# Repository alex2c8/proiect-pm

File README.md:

# ATmega DX-Ball

[DX-Ball](https://en.wikipedia.org/wiki/DX-Ball) on ATmega324A µC ([wiki](https://ocw.cs.pub.ro/courses/pm/prj2017/ddragomir/dx_ball)).

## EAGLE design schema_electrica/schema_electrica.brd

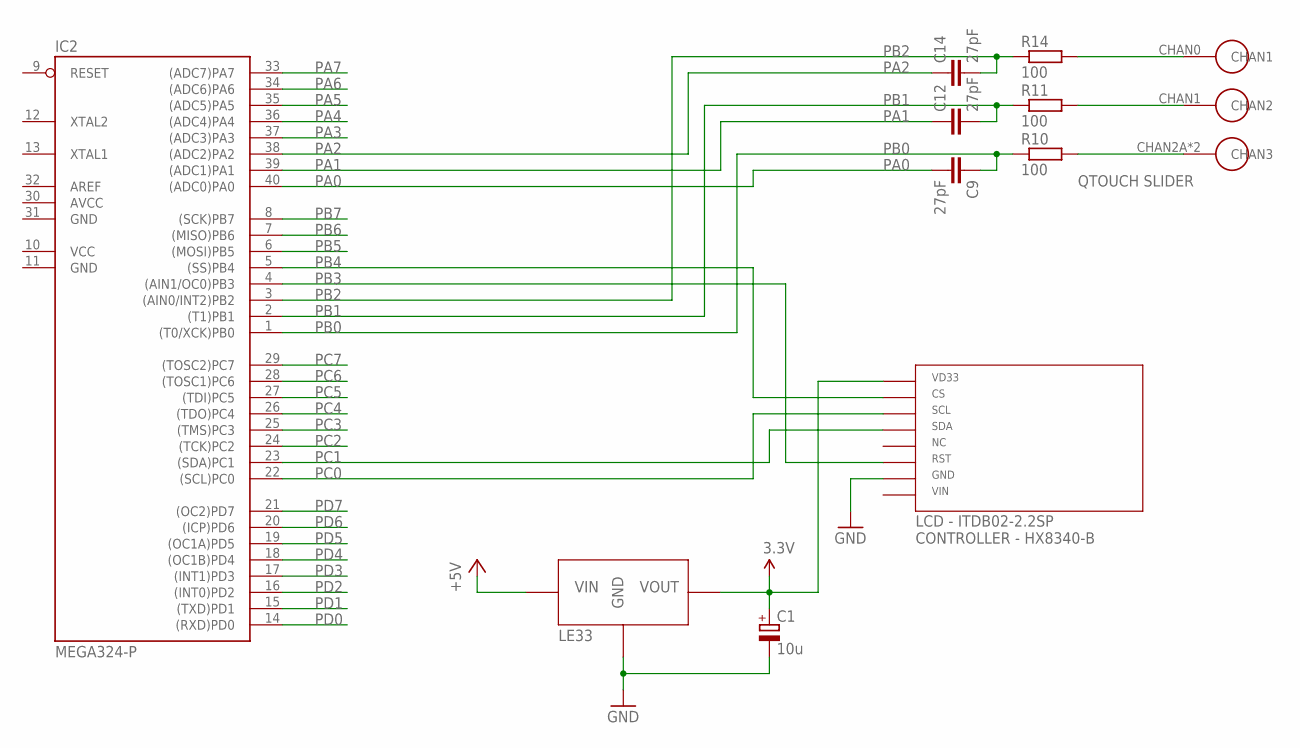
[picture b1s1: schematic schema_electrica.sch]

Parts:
C1: 10u; E2,5-5
C9, C12, C14: 27pF; C1206
IC2: MEGA324-P; DIL40
R10, R11, R14: 100; M1206
U$1: QT_SLIDER

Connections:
3.3V: C1.+
AVCC: IC2.30 (AVCC)
GND: C1.-, IC2.11 (GND), IC2.31 (GND)
unnamed: R14.2, U$1.CHAN0 (CHAN1)
unnamed: R11.2, U$1.CHAN1 (CHAN2)
unnamed: R10.2, U$1.CHAN2A (CHAN3), U$1.CHAN2B (CHAN3)
PA0: C9.2, IC2.40 ((ADC0)PA0)
PA1: C12.1, IC2.39 ((ADC1)PA1)
PA2: C14.1, IC2.38 ((ADC2)PA2)
PA3: IC2.37 ((ADC3)PA3)
PA4: IC2.36 ((ADC4)PA4)
PA5: IC2.35 ((ADC5)PA5)
PA6: IC2.34 ((ADC6)PA6)
PA7: IC2.33 ((ADC7)PA7)
PB0: C9.1, IC2.1 ((T0/XCK)PB0), R10.1
PB1: C12.2, IC2.2 ((T1)PB1), R11.1
PB2: C14.2, IC2.3 ((AIN0/INT2)PB2), R14.1
PB3: IC2.4 ((AIN1/OC0)PB3)
PB4: IC2.5 ((SS)PB4)
PB5: IC2.6 ((MOSI)PB5)
PB6: IC2.7 ((MISO)PB6)
PB7: IC2.8 ((SCK)PB7)
PC0: IC2.22 ((SCL)PC0)
PC1: IC2.23 ((SDA)PC1)
PC2: IC2.24 ((TCK)PC2)
PC3: IC2.25 ((TMS)PC3)
PC4: IC2.26 ((TDO)PC4)
PC5: IC2.27 ((TDI)PC5)
PC6: IC2.28 ((TOSC1)PC6)
PC7: IC2.29 ((TOSC2)PC7)
PD0: IC2.14 ((RXD)PD0)
PD1: IC2.15 ((TXD)PD1)
PD2: IC2.16 ((INT0)PD2)
PD3: IC2.17 ((INT1)PD3)
PD4: IC2.18 ((OC1B)PD4)
PD5: IC2.19 ((OC1A)PD5)
PD6: IC2.20 ((ICP)PD6)
PD7: IC2.21 ((OC2)PD7)
VCC: IC2.10 (VCC)

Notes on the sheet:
VD33
SCL
SDA
RST
GND
VIN
LCD - ITDB02-2.2SP CONTROLLER - HX8340-B
QTOUCH SLIDER
VOUT
LE33

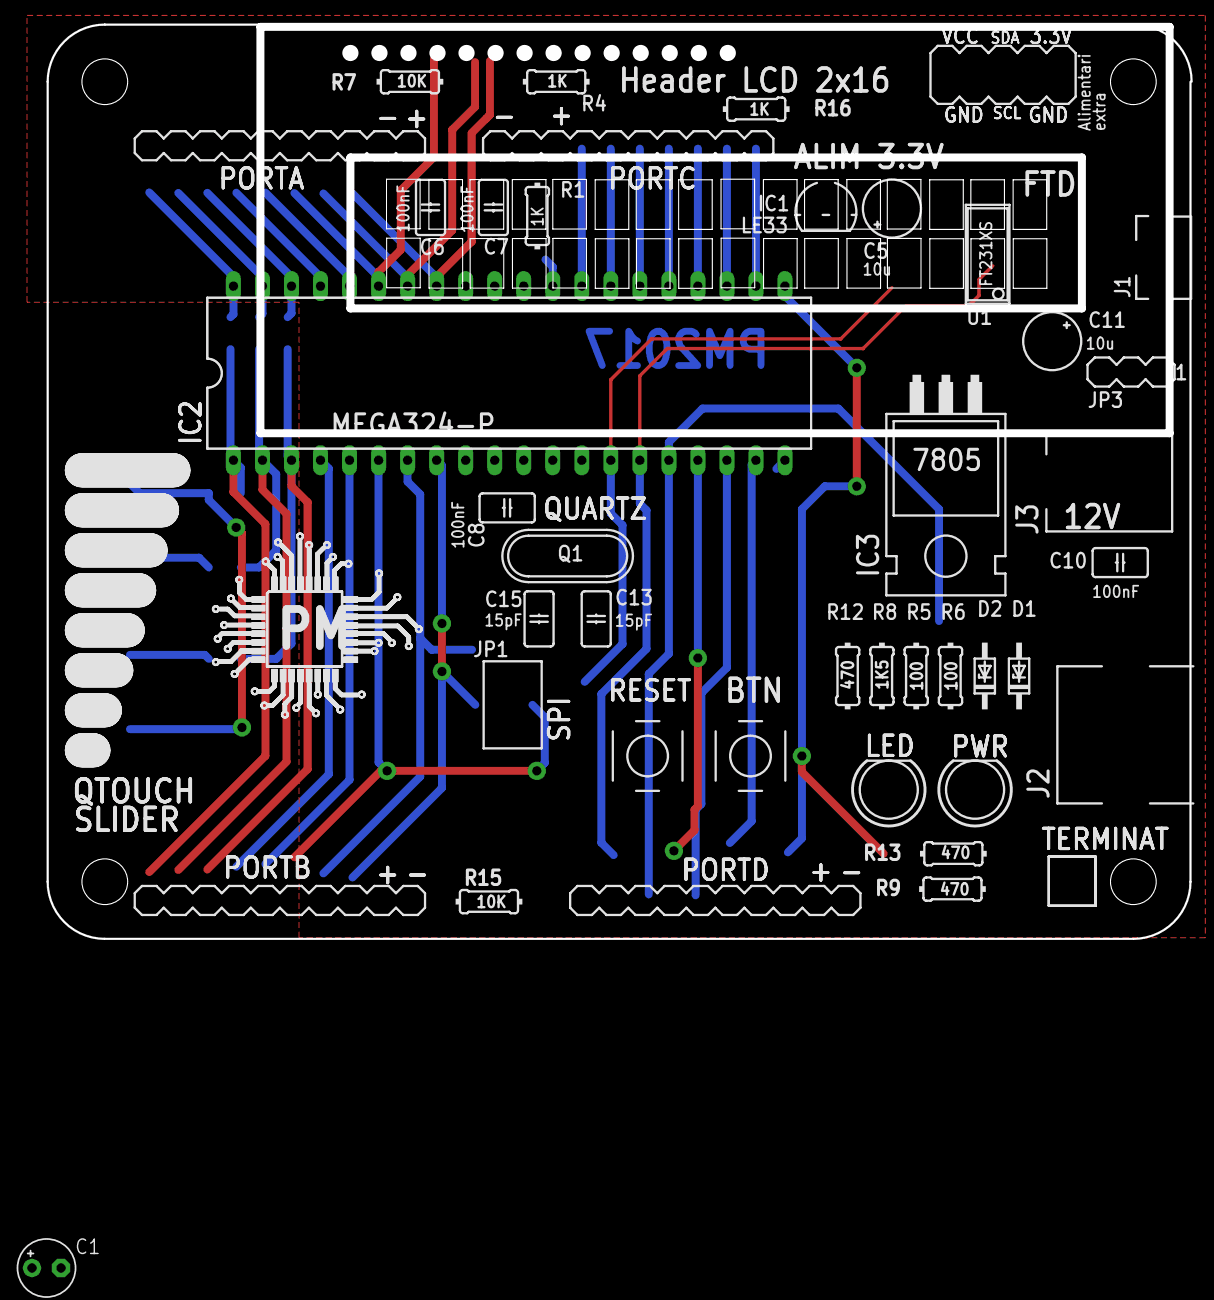
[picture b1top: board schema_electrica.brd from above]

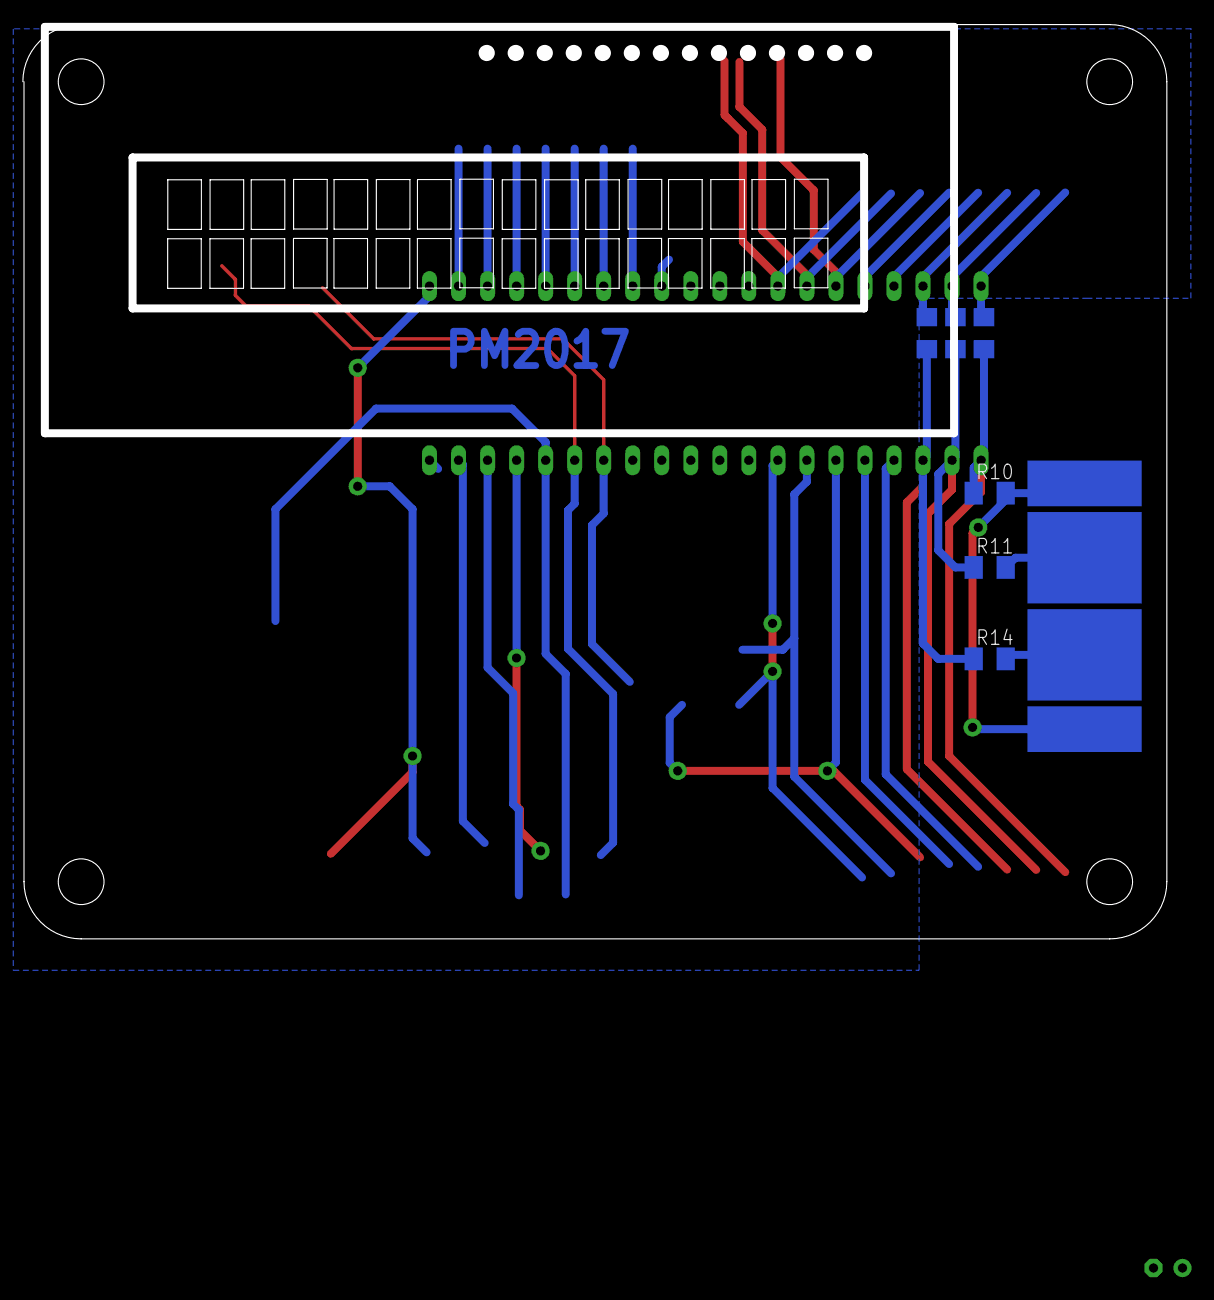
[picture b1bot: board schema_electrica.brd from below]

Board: 2 copper layers, 100.1 x 80.0 mm, 9 parts (7 on the bottom side), 10 nets.

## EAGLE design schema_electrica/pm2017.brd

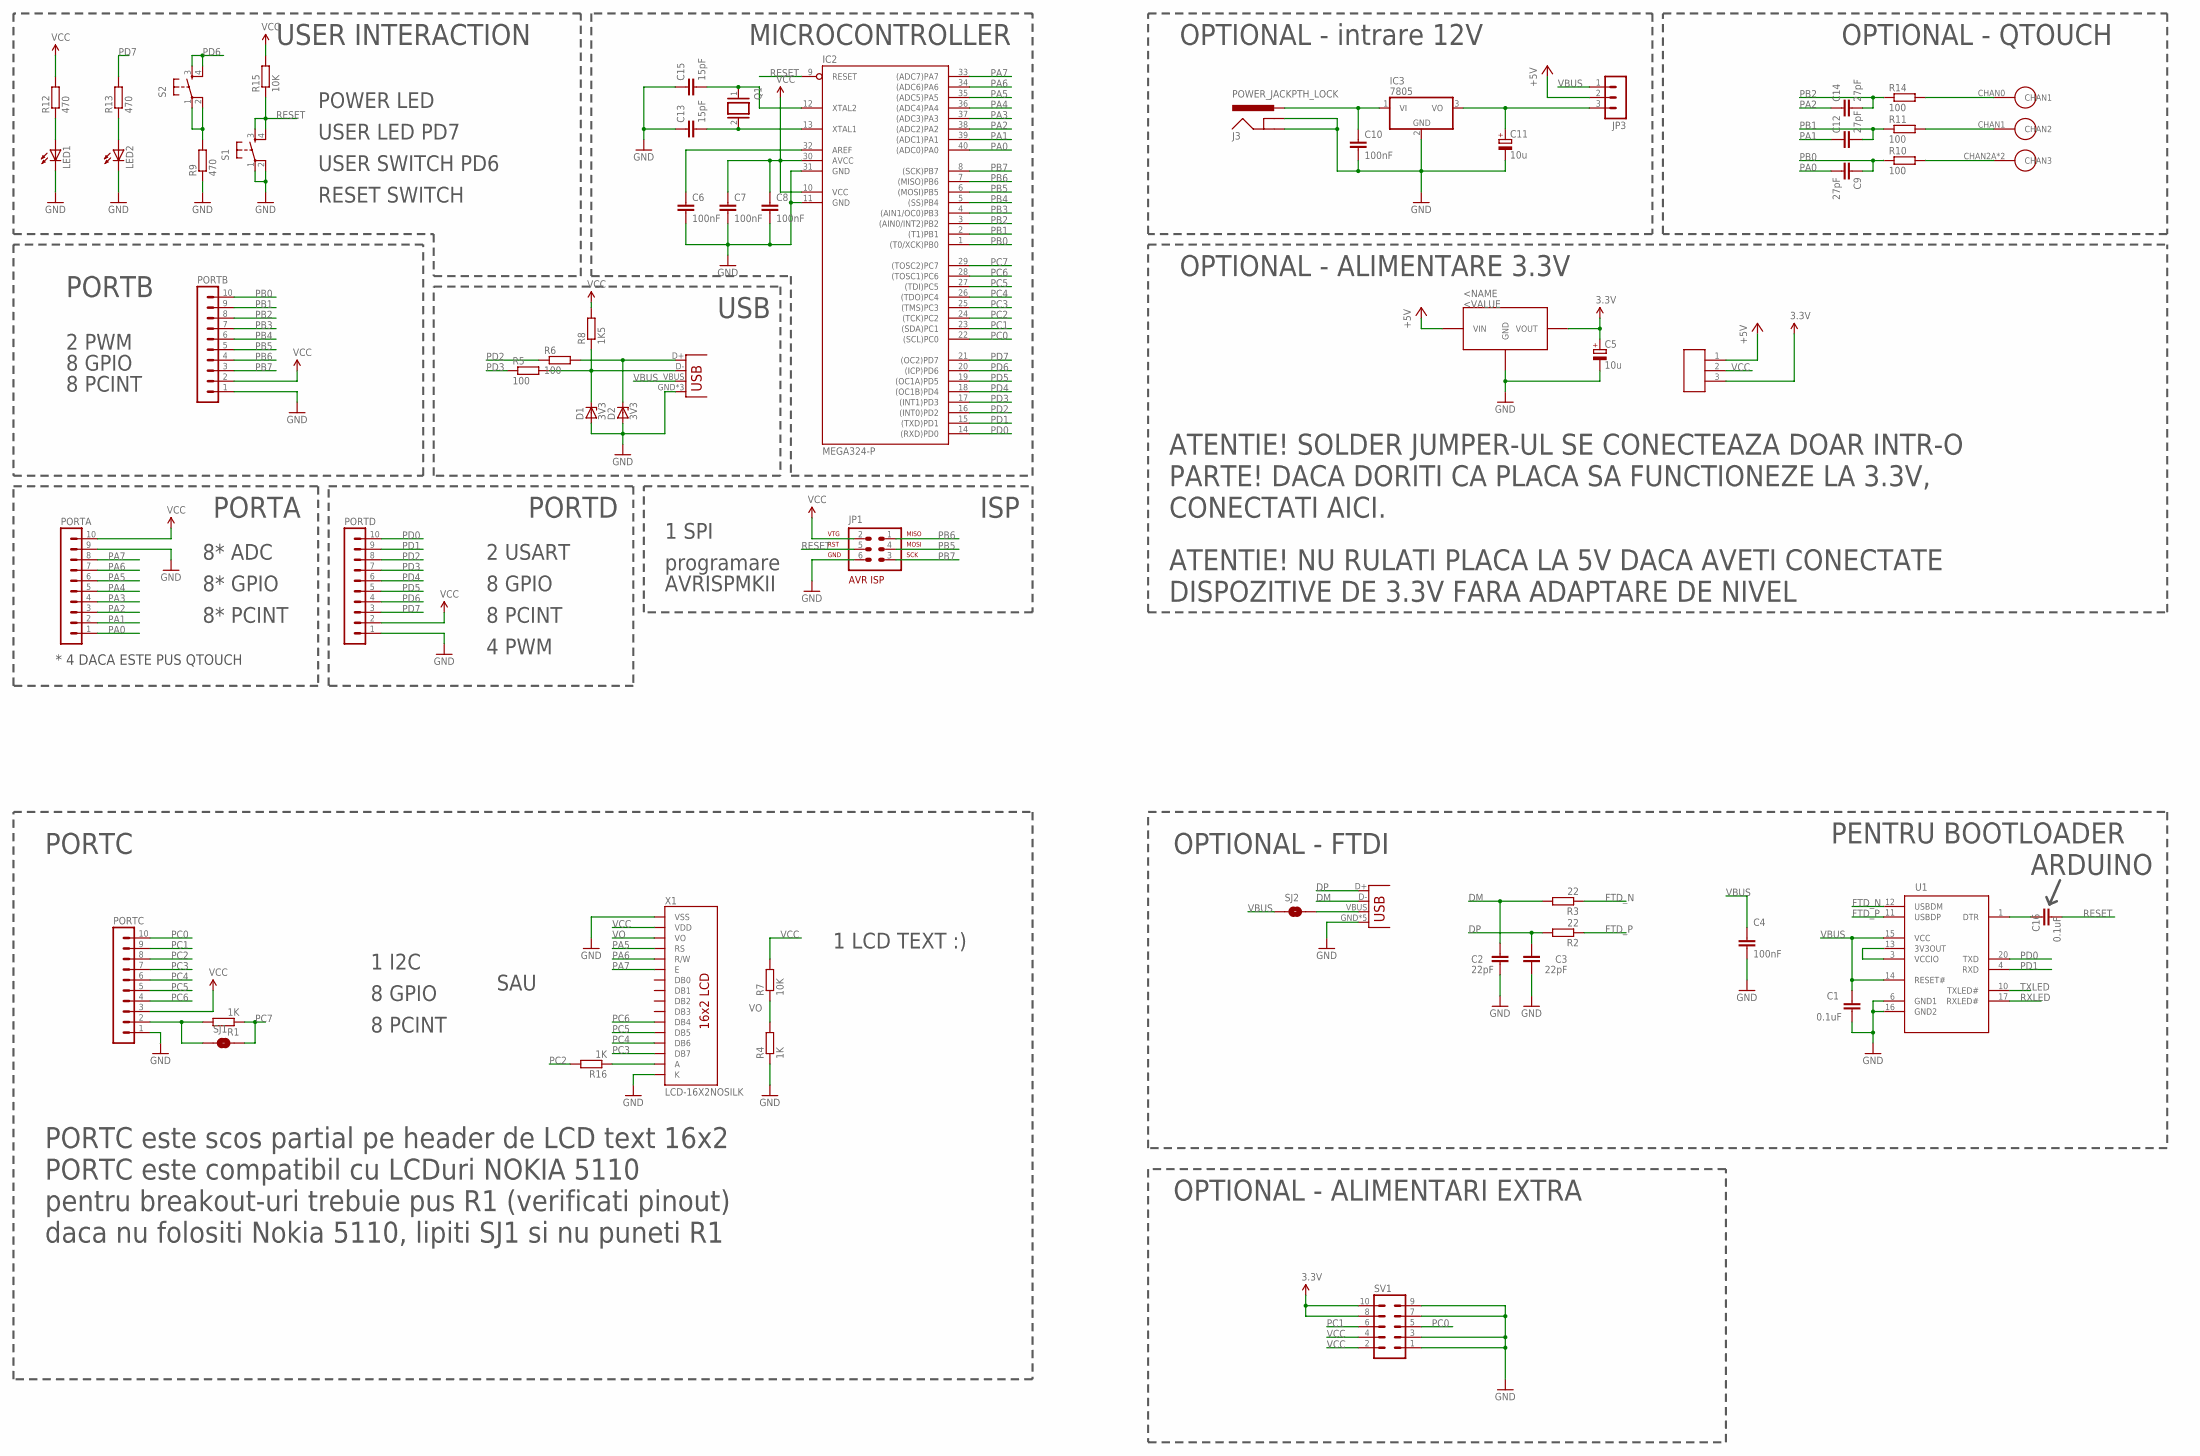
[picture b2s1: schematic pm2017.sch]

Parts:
C1, C16: 0.1uF; C0603
C2, C3: 22pF; C0603
C4: 100nF; C0603
C5, C11: 10u; E2,5-5
C6, C7, C8: 100nF; C025-025X050
C9, C12, C14: 27pF; C1206
C10: 100nF; C025-025X050@1
C13, C15: 15pF; C025-025X050
D1, D2: 3V3; DO34Z7
IC1: LE33; TO92
IC2: MEGA324-P; DIL40
IC3: 7805; TO22H_NOHOLE
J1: USB; ZX62D-B-5PA8
J2: USBPTH; USB-B-PTH
J3: POWER_JACKPTH_LOCK; POWER_JACK_PTH_LOCK
JP1: AVR-ISP-6
JP2: SJUMPER; SJUMPER_PACK
JP3: MA03-1
LED1, LED2: LED5MM
PORTA: MA10-1
PORTB: MA10-1
PORTC: MA10-1
PORTD: MA10-1
Q1: XTAL/S; QS
R1, R4, R16: 1K; 0204/7
R2, R3: 22; R0603
R5, R6: 100; 0204/7
R7, R15: 10K; 0204/7
R8: 1K5; 0204/7
R9, R12, R13: 470; 0204/7
R10, R11, R14: 100; M1206
S1, S2: TAC_SWITCHPTH; TACTILE-PTH
SJ1, SJ2: SOLDERJUMPERNC; SJ-NC
SV1: MA05-2
U1: FT231XS; SSOP20
U$1: QT_SLIDER
X1: LCD-16X2NOSILK; LCD-16X2_NOSILK

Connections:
3.3V: C5.+, IC1.1 (VOUT), JP2.3, SV1.8, SV1.10
+5V: IC1.3 (VIN), JP2.1, JP3.2
DM: C2.2, J1.D-, R3.2
DP: C3.2, J1.D+, R2.2
FTD_N: R3.1, U1.12 (USBDM)
FTD_P: R2.1, U1.11 (USBDP)
GND: C1.2, C2.1, C3.1, C4.2, C5.-, C6.2, C7.2, C8.2, C10.2, C11.-, C13.1, C15.1, D1.A, D2.A, IC1.2 (GND), IC2.11 (GND), IC2.31 (GND), IC3.2 (GND), J1.GND, J1.P$8 (GND), J1.P$9 (GND), J1.P$10 (GND), J1.P$11 (GND), J2.GND, J2.P$1 (GND), J2.P$2 (GND), J3.GND, J3.GNDBREAK, JP1.6, LED1.K (C), LED2.K (C), PORTA.9, PORTB.1, PORTC.1, PORTD.1, R4.1, R9.1, S1.1, S1.2, SV1.1, SV1.3, SV1.7, SV1.9, U1.6 (GND1), U1.16 (GND2), X1.1 (VSS), X1.16 (K)
unnamed: LED2.A, R13.1
unnamed: LED1.A, R12.1
unnamed: PORTC.2, R1.2, SJ1.1
unnamed: J1.VBUS, SJ2.2
unnamed: R14.2, U$1.CHAN0 (CHAN1)
unnamed: R11.2, U$1.CHAN1 (CHAN2)
unnamed: R10.2, U$1.CHAN2A (CHAN3), U$1.CHAN2B (CHAN3)
unnamed: R16.1, X1.15 (A)
unnamed: C16.1, U1.1 (DTR)
unnamed: U1.3 (VCCIO), U1.13 (3V3OUT)
unnamed: D2.C, J2.D+, R6.2
unnamed: D1.C, J2.D-, R5.2, R8.1
unnamed: C10.1, IC3.1 (VI), J3.PWR
unnamed: R9.2, S2.1, S2.2
unnamed: C11.+, IC3.3 (VO), JP3.3
unnamed: C6.1, IC2.32 (AREF)
unnamed: C13.2, IC2.13 (XTAL1), Q1.2
unnamed: C15.2, IC2.12 (XTAL2), Q1.1
PA0: C9.2, IC2.40 ((ADC0)PA0), PORTA.1
PA1: C12.1, IC2.39 ((ADC1)PA1), PORTA.2
PA2: C14.1, IC2.38 ((ADC2)PA2), PORTA.3
PA3: IC2.37 ((ADC3)PA3), PORTA.4
PA4: IC2.36 ((ADC4)PA4), PORTA.5
PA5: IC2.35 ((ADC5)PA5), PORTA.6, X1.4 (RS)
PA6: IC2.34 ((ADC6)PA6), PORTA.7, X1.5 (R/W)
PA7: IC2.33 ((ADC7)PA7), PORTA.8, X1.6 (E)
PB0: C9.1, IC2.1 ((T0/XCK)PB0), PORTB.10, R10.1
PB1: C12.2, IC2.2 ((T1)PB1), PORTB.9, R11.1
PB2: C14.2, IC2.3 ((AIN0/INT2)PB2), PORTB.8, R14.1
PB3: IC2.4 ((AIN1/OC0)PB3), PORTB.7
PB4: IC2.5 ((SS)PB4), PORTB.6
PB5: IC2.6 ((MOSI)PB5), JP1.4, PORTB.5
PB6: IC2.7 ((MISO)PB6), JP1.1, PORTB.4
PB7: IC2.8 ((SCK)PB7), JP1.3, PORTB.3
PC0: IC2.22 ((SCL)PC0), PORTC.10, SV1.5
PC1: IC2.23 ((SDA)PC1), PORTC.9, SV1.6
PC2: IC2.24 ((TCK)PC2), PORTC.8, R16.2
PC3: IC2.25 ((TMS)PC3), PORTC.7, X1.14 (DB7)
PC4: IC2.26 ((TDO)PC4), PORTC.6, X1.13 (DB6)
PC5: IC2.27 ((TDI)PC5), PORTC.5, X1.12 (DB5)
PC6: IC2.28 ((TOSC1)PC6), PORTC.4, X1.11 (DB4)
PC7: IC2.29 ((TOSC2)PC7), R1.1, SJ1.2
PD0: IC2.14 ((RXD)PD0), PORTD.10, U1.20 (TXD)
PD1: IC2.15 ((TXD)PD1), PORTD.9, U1.4 (RXD)
PD2: IC2.16 ((INT0)PD2), PORTD.8, R6.1
PD3: IC2.17 ((INT1)PD3), PORTD.7, R5.1
PD4: IC2.18 ((OC1B)PD4), PORTD.6
PD5: IC2.19 ((OC1A)PD5), PORTD.5
PD6: IC2.20 ((ICP)PD6), PORTD.4, S2.3, S2.4
PD7: IC2.21 ((OC2)PD7), PORTD.3, R13.2
RESET: C16.2, IC2.9 (RESET), JP1.5, R15.1, S1.3, S1.4
RXLED: U1.17 (RXLED#)
TXLED: U1.10 (TXLED#)
VBUS: C1.1, C4.1, J2.VBUS, JP3.1, SJ2.1, U1.14 (RESET#), U1.15 (VCC)
VCC: C7.1, C8.1, IC2.10 (VCC), IC2.30 (AVCC), JP1.2, JP2.2, PORTA.10, PORTB.2, PORTC.3, PORTD.2, R7.2, R8.2, R12.2, R15.2, SV1.2, SV1.4, X1.2 (VDD)
VO: R4.2, R7.1, X1.3 (VO)

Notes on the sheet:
8* ADC
8* GPIO
8* PCINT
* 4 DACA ESTE PUS QTOUCH
1 I2C
8 GPIO
8 PCINT
2 USART
4 PWM
1 SPI
programare
AVRISPMKII
PORTA
PORTC
PORTD
USB
ISP
POWER LED
USER LED PD7
USER SWITCH PD6
RESET SWITCH
USER INTERACTION
MICROCONTROLLER
OPTIONAL - intrare 12V
OPTIONAL - QTOUCH
OPTIONAL - ALIMENTARE 3.3V
ATENTIE! SOLDER JUMPER-UL SE CONECTEAZA DOAR INTR-O
PARTE! DACA DORITI CA PLACA SA FUNCTIONEZE LA 3.3V,
CONECTATI AICI.
ATENTIE! NU RULATI PLACA LA 5V DACA AVETI CONECTATE
DISPOZITIVE DE 3.3V FARA ADAPTARE DE NIVEL
PORTB
2 PWM
1 LCD TEXT :)
SAU
OPTIONAL - FTDI
PORTC este compatibil cu LCDuri NOKIA 5110
pentru breakout-uri trebuie pus R1 (verificati pinout)
daca nu folositi Nokia 5110, lipiti SJ1 si nu puneti R1
PORTC este scos partial pe header de LCD text 16x2

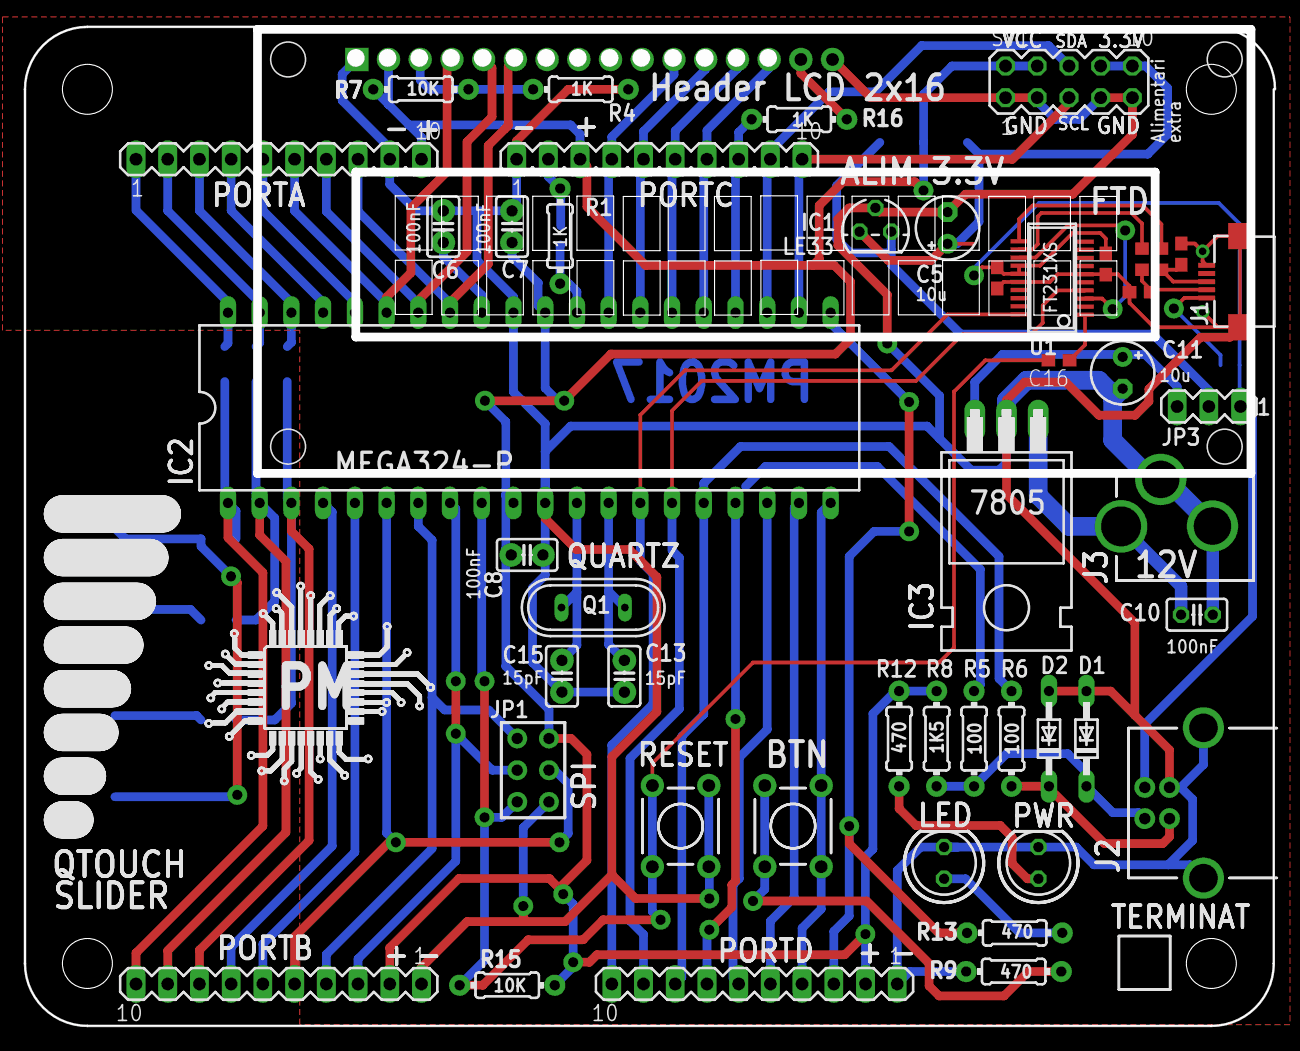
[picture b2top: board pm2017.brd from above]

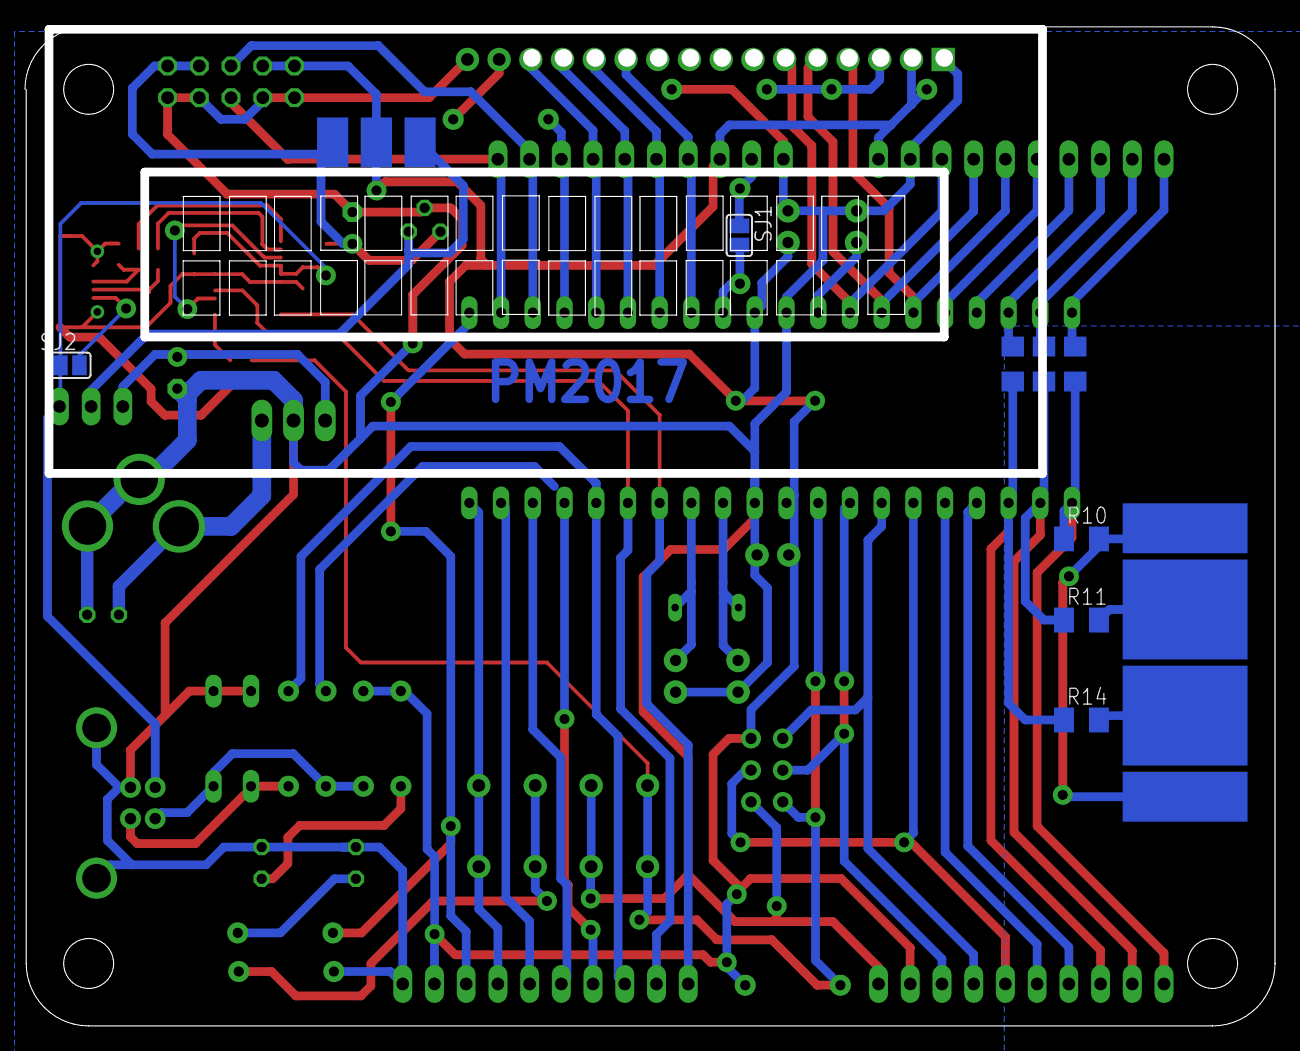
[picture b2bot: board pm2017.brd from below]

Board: 2 copper layers, 100.1 x 80.0 mm, 58 parts (10 on the bottom side), 61 nets.

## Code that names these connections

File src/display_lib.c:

#include "display_lib.h"

void LCD_Writ_Bus(char VH, char VL, uint8_t mode)
{
	switch (mode)
	{
		case 1:
			if (VH == 1)
				sbi(P_SDA, B_SDA);
			else
				cbi(P_SDA, B_SDA);
			pulse_low(P_SCL, B_SCL);


			if (VL & 0x80)
				sbi(P_SDA, B_SDA);
			else
				cbi(P_SDA, B_SDA);
			pulse_low(P_SCL, B_SCL);

			if (VL & 0x40)
				sbi(P_SDA, B_SDA);
			else
				cbi(P_SDA, B_SDA);
			pulse_low(P_SCL, B_SCL);

			if (VL & 0x20)
				sbi(P_SDA, B_SDA);
			else
				cbi(P_SDA, B_SDA);
			pulse_low(P_SCL, B_SCL);

			if (VL & 0x10)
				sbi(P_SDA, B_SDA);
			else
				cbi(P_SDA, B_SDA);
			pulse_low(P_SCL, B_SCL);

			if (VL & 0x08)
				sbi(P_SDA, B_SDA);
			else
				cbi(P_SDA, B_SDA);
			pulse_low(P_SCL, B_SCL);

			if (VL & 0x04)
				sbi(P_SDA, B_SDA);
			else
				cbi(P_SDA, B_SDA);
			pulse_low(P_SCL, B_SCL);

			if (VL & 0x02)
				sbi(P_SDA, B_SDA);
			else
				cbi(P_SDA, B_SDA);
			pulse_low(P_SCL, B_SCL);

			if (VL & 0x01)
				sbi(P_SDA, B_SDA);
			else
				cbi(P_SDA, B_SDA);
			pulse_low(P_SCL, B_SCL);

			break;
	}
}

void LCD_Write_COM(char VL)
{
	LCD_Writ_Bus(0x00, VL, DISPLAY_TRANSFER_MODE);
}

void LCD_Write_DATA_hl(char VH,char VL)
{
	LCD_Writ_Bus(0x01, VH, DISPLAY_TRANSFER_MODE);
	LCD_Writ_Bus(0x01, VL, DISPLAY_TRANSFER_MODE);
}

void LCD_Write_DATA(char VL)
{
	LCD_Writ_Bus(0x01 , VL, DISPLAY_TRANSFER_MODE);
}

void LCD_Write_COM_DATA(char com1, int dat1)
{
    LCD_Write_COM(com1);
    LCD_Write_DATA_hl(dat1 >> 8 , dat1);
}

void _set_direction_registers(uint8_t mode)
{
	DDRD = 0xFF;
	if (mode == 16) {
		DDRB |= 0x3F;
		DDRC |= 0x03;
	}
}



void _low_level_init()
{
	sbi(P_RST, B_RST);
	_delay_ms(5);
	cbi(P_RST, B_RST);
	_delay_ms(15);
	sbi(P_RST, B_RST);
	_delay_ms(15);

	cbi(P_CS, B_CS);

	LCD_Write_COM(0xC1);
	LCD_Write_DATA(0xFF);
	LCD_Write_DATA(0x83);
	LCD_Write_DATA(0x40);
	LCD_Write_COM(0x11);
	_delay_ms(100);
	LCD_Write_COM(0xCA);
	LCD_Write_DATA(0x70);
	LCD_Write_DATA(0x00);
	LCD_Write_DATA(0xD9);
	LCD_Write_DATA(0x01);
	LCD_Write_DATA(0x11);

	LCD_Write_COM(0xC9);
	LCD_Write_DATA(0x90);
	LCD_Write_DATA(0x49);
	LCD_Write_DATA(0x10);
	LCD_Write_DATA(0x28);
	LCD_Write_DATA(0x28);
	LCD_Write_DATA(0x10);
	LCD_Write_DATA(0x00);
	LCD_Write_DATA(0x06);
	_delay_ms(20);
	LCD_Write_COM(0xC2);
	LCD_Write_DATA(0x60);
	LCD_Write_DATA(0x71);
	LCD_Write_DATA(0x01);
	LCD_Write_DATA(0x0E);
	LCD_Write_DATA(0x05);
	LCD_Write_DATA(0x02);
	LCD_Write_DATA(0x09);
	LCD_Write_DATA(0x31);
	LCD_Write_DATA(0x0A);

	LCD_Write_COM(0xc3);
	LCD_Write_DATA(0x67);
	LCD_Write_DATA(0x30);
	LCD_Write_DATA(0x61);
	LCD_Write_DATA(0x17);
	LCD_Write_DATA(0x48);
	LCD_Write_DATA(0x07);
	LCD_Write_DATA(0x05);
	LCD_Write_DATA(0x33);
	_delay_ms(10);
	LCD_Write_COM(0xB5);
	LCD_Write_DATA(0x35);
	LCD_Write_DATA(0x20);
	LCD_Write_DATA(0x45);

	LCD_Write_COM(0xB4);
	LCD_Write_DATA(0x33);
	LCD_Write_DATA(0x25);
	LCD_Write_DATA(0x4c);
	_delay_ms(10);
	LCD_Write_COM(0x3a);
	LCD_Write_DATA(0x05);
	LCD_Write_COM(0x29);
	_delay_ms(10);
	LCD_Write_COM(0x2a);
	LCD_Write_DATA(0x00);
	LCD_Write_DATA(0x00);
	LCD_Write_DATA(0x00);
	LCD_Write_DATA(0xaf);
	LCD_Write_COM(0x2b);
	LCD_Write_DATA(0x00);
	LCD_Write_DATA(0x00);
	LCD_Write_DATA(0x00);
	LCD_Write_DATA(0xdb);
	LCD_Write_COM(0x2c);

	sbi (P_CS, B_CS);
}

void init_lcd(uint8_t orientation)
{
	g_disp_orient = orientation;

	// SDA is on PC1
	P_SDA = &PORTC;
	B_SDA = (1 << PC1);
	DDRC |= B_SDA;

	// SCL is on PC0
	P_SCL = &PORTC;
	B_SCL = (1 << PC0);
	DDRC |= B_SCL;

	// CS (SS) is on PB4
	P_CS = &PORTB;
	B_CS = (1 << PB4);
	DDRB |= B_CS;

	// RST is on PB3
	P_RST = &PORTB;
	B_RST = (1 << PB3);
	DDRB |= B_RST;

	_low_level_init();

	set_foreground_color(255, 255, 255);
	set_background_color(0, 0, 0);
}



void setXY(word_t x1, word_t y1, word_t x2, word_t y2)
{
	if (g_disp_orient == LANDSCAPE)
	{
		swap(word_t, x1, y1);
		swap(word_t, x2, y2)
		y1 = DISPLAY_Y_SIZE - y1;
		y2 = DISPLAY_Y_SIZE - y2;
		swap(word_t, y1, y2)
	}

	LCD_Write_COM(0x2a);
  	LCD_Write_DATA(x1>>8);
  	LCD_Write_DATA(x1);
  	LCD_Write_DATA(x2>>8);
  	LCD_Write_DATA(x2);
	LCD_Write_COM(0x2b);
  	LCD_Write_DATA(y1>>8);
  	LCD_Write_DATA(y1);
  	LCD_Write_DATA(y2>>8);
  	LCD_Write_DATA(y2);
	LCD_Write_COM(0x2c);
}

void resetXY()
{
	if (g_disp_orient == PORTRAIT)
		setXY(0, 0, DISPLAY_X_SIZE, DISPLAY_Y_SIZE);
	else
		setXY(0, 0, DISPLAY_Y_SIZE, DISPLAY_X_SIZE);
}



void fill_screen(uint8_t r, uint8_t g, uint8_t b)
{
	long i;
	long screen_size;
	char ch, cl;

	ch = ((r & 248) | g >> 5);
	cl = ((g & 28) << 3 | b >> 3);

	cbi(P_CS, B_CS);
	resetXY();

	screen_size = (DISPLAY_X_SIZE + 1) * (DISPLAY_Y_SIZE + 1);

	for (i = 0; i < screen_size; i++) {
		LCD_Writ_Bus(1, ch, DISPLAY_TRANSFER_MODE);
		LCD_Writ_Bus(1, cl, DISPLAY_TRANSFER_MODE);
	}

	sbi(P_CS, B_CS);
}

void clear_screen()
{
	long i;
	long screen_size;

	cbi(P_CS, B_CS);
	resetXY();

	screen_size = (DISPLAY_X_SIZE + 1) * (DISPLAY_Y_SIZE + 1);

	for (i = 0; i < screen_size; i++) {
		LCD_Writ_Bus(1, 0, DISPLAY_TRANSFER_MODE);
		LCD_Writ_Bus(1, 0, DISPLAY_TRANSFER_MODE);
	}

	sbi(P_CS, B_CS);
}



void set_pixel(uint8_t r, uint8_t g, uint8_t b)
{
	// rrrrr gggggg bbbbb
	LCD_Write_DATA_hl(((r & 248) | g >> 5), ((g & 28) << 3 | b >> 3));
}

void draw_pixel(int x, int y)
{
	cbi(P_CS, B_CS);

	setXY(x, y, x, y);

	set_pixel(g_fcolor_red, g_fcolor_green, g_fcolor_blue);

	sbi(P_CS, B_CS);

	resetXY();
}


void set_foreground_color(uint8_t r, uint8_t g, uint8_t b)
{
	g_fcolor_red = r;
	g_fcolor_green = g;
	g_fcolor_blue = b;
}

void set_background_color(uint8_t r, uint8_t g, uint8_t b)
{
	g_bcolor_red = r;
	g_bcolor_green = g;
	g_bcolor_blue = b;
}



void set_font(uint8_t *font)
{
	g_font.font = font;
	g_font.x_size = fontbyte(0);
	g_font.y_size = fontbyte(1);
	g_font.offset = fontbyte(2);
	g_font.numchars = fontbyte(3);
}

void print_char(uint8_t c, int x, int y)
{
	uint8_t i, ch;
	word_t j, k;
	word_t temp;

	cbi(P_CS, B_CS);

	if (g_disp_orient == PORTRAIT) {
		setXY(x, y, x + g_font.x_size - 1, y + g_font.y_size - 1);

		temp = ((c-g_font.offset) * ((g_font.x_size/8) * g_font.y_size)) + 4;

		for (j = 0; j < ((g_font.x_size/8) * g_font.y_size); j++) {

			ch = pgm_read_byte(&g_font.font[temp]);

			for (i = 0; i < 8; i++) {
				if ((ch & (1 << (7 - i))) != 0)
					set_pixel(g_fcolor_red, g_fcolor_green, g_fcolor_blue);
				else
					set_pixel(g_bcolor_red, g_bcolor_green, g_bcolor_blue);
			}

			temp++;
		}
	}
	// orientation == LANDSCAPE
	else {
		temp = ((c-g_font.offset) * ((g_font.x_size/8) * g_font.y_size)) + 4;

		for (j = 0; j < ((g_font.x_size/8)*g_font.y_size); j += (g_font.x_size/8)) {

			setXY(x, y + (j/(g_font.x_size/8)), x + g_font.x_size-1, y + (j/(g_font.x_size/8)));

			for (k = (g_font.x_size/8) - 1; k >= 0; k--) {

				ch = pgm_read_byte(&g_font.font[temp+k]);

				for (i = 0; i < 8; i++)
				{
					if ((ch & (1 << i)) != 0)
						set_pixel(g_fcolor_red, g_fcolor_green, g_fcolor_blue);
					else
						set_pixel(g_bcolor_red, g_bcolor_green, g_bcolor_blue);
				}
			}

			temp += (g_font.x_size / 8);
		}
	}

	sbi(P_CS, B_CS);
	resetXY();
}

void print_string(char *st, int x, int y, int deg)
{
	int stl, i;

	stl = strlen(st);

	if (g_disp_orient == PORTRAIT) {
		if (x == RIGHT)
			x = (DISPLAY_X_SIZE + 1) - (stl * g_font.x_size);

		if (x == CENTER)
			x = ((DISPLAY_X_SIZE + 1) - (stl * g_font.x_size)) / 2;
	}
	// orientation == LANDSCAPE
	else
	{
		if (x == RIGHT)
			x = (DISPLAY_Y_SIZE + 1) - (stl * g_font.x_size);

		if (x == CENTER)
			x = ((DISPLAY_Y_SIZE + 1) - (stl * g_font.x_size)) / 2;
	}

	for (i = 0; i < stl; i++) {
		if (deg == 0)
			print_char(*st++, x + (i * (g_font.x_size)), y);
		// else
		// 	rotateChar(*st++, x, y, i, deg);
	}
}



void draw_straight_line(int x, int y, int l, int type)
{
	int i;
	char ch, cl;

	int limit = l;

	ch = ((g_fcolor_red & 248) | g_fcolor_green >> 5);
	cl = ((g_fcolor_green & 28) << 3 | g_fcolor_blue >> 3);

	cbi(P_CS, B_CS);

	if (type == HORIZONTAL_LINE) {
		limit = l + 1;
		setXY(x, y, x + l, y);
	} else if (type == VERTICAL_LINE) {
		limit = l;
		setXY(x, y, x, y + l);
	}

	for (i = 0; i < limit; i++)
		LCD_Write_DATA_hl(ch, cl);

	sbi(P_CS, B_CS);
	resetXY();
}

void draw_empty_rectangle(int x1, int y1, int x2, int y2)
{
	if (x1 > x2)
		swap(int, x1, x2);

	if (y1 > y2)
		swap(int, y1, y2);

	draw_straight_line(x1, y1, x2 - x1, HORIZONTAL_LINE);
	draw_straight_line(x1, y2, x2 - x1, HORIZONTAL_LINE);
	draw_straight_line(x1, y1, y2 - y1, VERTICAL_LINE);
	draw_straight_line(x2, y1, y2 - y1, VERTICAL_LINE);
}


void draw_filled_rectangle(int x1, int y1, int x2, int y2)
{
	int i;

	if (x1 > x2)
		swap(int, x1, x2);

	if (y1 > y2)
		swap(int, y1, y2);

	if (g_disp_orient == PORTRAIT) {
		for (i = 0; i < ((y2 - y1) / 2) + 1; i++) {
			draw_straight_line(x1, y1 + i, x2 - x1, HORIZONTAL_LINE);
			draw_straight_line(x1, y2 - i, x2 - x1, HORIZONTAL_LINE);
		}
	} else {
		for (i = 0; i < ((x2 - x1) / 2) + 1; i++) {
			draw_straight_line(x1 + i, y1, y2 - y1, VERTICAL_LINE);
			draw_straight_line(x2 - i, y1, y2 - y1, VERTICAL_LINE);
		}
	}
}

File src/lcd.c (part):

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void LCD_Writ_Bus(char VH, char VL, uint8_t mode)
{
	if (VH == 1)
		sbi(PORTB, (1 << PB0));
	else
		cbi(PORTB, (1 << PB0));
	pulse_low(PORTB, (1 << PB1));


	if (VL & 0x80)
		sbi(PORTB, (1 << PB0));
	else
		cbi(PORTB, (1 << PB0));
	pulse_low(PORTB, (1 << PB1));

	if (VL & 0x40)
		sbi(PORTB, (1 << PB0));
	else
		cbi(PORTB, (1 << PB0));
	pulse_low(PORTB, (1 << PB1));

	if (VL & 0x20)
		sbi(PORTB, (1 << PB0));
	else
		cbi(PORTB, (1 << PB0));
	pulse_low(PORTB, (1 << PB1));

	if (VL & 0x10)
		sbi(PORTB, (1 << PB0));
	else
		cbi(PORTB, (1 << PB0));
	pulse_low(PORTB, (1 << PB1));

	if (VL & 0x08)
		sbi(PORTB, (1 << PB0));
	else
		cbi(PORTB, (1 << PB0));
	pulse_low(PORTB, (1 << PB1));

	if (VL & 0x04)
		sbi(PORTB, (1 << PB0));
	else
		cbi(PORTB, (1 << PB0));
	pulse_low(PORTB, (1 << PB1));

	if (VL & 0x02)
		sbi(PORTB, (1 << PB0));
	else
		cbi(PORTB, (1 << PB0));
	pulse_low(PORTB, (1 << PB1));

	if (VL & 0x01)
		sbi(PORTB, (1 << PB0));
	else
		cbi(PORTB, (1 << PB0));
	pulse_low(PORTB, (1 << PB1));
}

void LCD_Write_COM(char VL)
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
void _low_level_init()
{
	sbi(PORTB, (1 << PB3));
	_delay_ms(5);
	cbi(PORTB, (1 << PB3));
	_delay_ms(15);
	sbi(PORTB, (1 << PB3));
	_delay_ms(15);

	cbi(PORTB, (1 << PB4));

	LCD_Write_COM(0xC1);
	LCD_Write_DATA(0xFF);
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	LCD_Write_DATA(0xdb);
	LCD_Write_COM(0x2c);

	sbi (PORTB, (1 << PB4));
}

void init_lcd(uint8_t orientation)
{
	g_disp_orient = orientation;

	// SDA is on PB0
	DDRB |= (1 << PB0);
	// SCL is on PB1
	DDRB |= (1 << PB1);
	// CS (SS) is on PB4
	DDRB |= (1 << PB4);
	// RST is on PB3
	DDRB |= (1 << PB3);

	_low_level_init();

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	ch = ((r & 248) | g >> 5);
	cl = ((g & 28) << 3 | b >> 3);

	cbi(PORTB, (1 << PB4));
	resetXY();

	screen_size = ((long)DISPLAY_X_SIZE + 1) * ((long)DISPLAY_Y_SIZE + 1);
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		LCD_Writ_Bus(1, cl, DISPLAY_TRANSFER_MODE);
	}

	sbi(PORTB, (1 << PB4));
}

void clear_screen()
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	long i;
	long screen_size;

	cbi(PORTB, (1 << PB4));
	resetXY();

	screen_size = ((long)DISPLAY_X_SIZE + 1) * ((long)DISPLAY_Y_SIZE + 1);
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		LCD_Writ_Bus(1, 0, DISPLAY_TRANSFER_MODE);
	}

	sbi(PORTB, (1 << PB4));
}

void clear_region(word_t x1, word_t y1, word_t x2, word_t y2)
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
void draw_pixel(int x, int y)
{
	cbi(PORTB, (1 << PB4));

	setXY(x, y, x, y);

	set_pixel(g_fcolor_red, g_fcolor_green, g_fcolor_blue);

	sbi(PORTB, (1 << PB4));

	resetXY();
}
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	word_t j, k;
	word_t temp;

	cbi(PORTB, (1 << PB4));

	if (g_disp_orient == PORTRAIT) {
		setXY(x, y, x + g_font.x_size - 1, y + g_font.y_size - 1);
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		}
	}

	sbi(PORTB, (1 << PB4));
	resetXY();
}

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	ch = ((g_fcolor_red & 248) | g_fcolor_green >> 5);
	cl = ((g_fcolor_green & 28) << 3 | g_fcolor_blue >> 3);

	cbi(PORTB, (1 << PB4));

	if (type == HORIZONTAL_LINE) {
		limit = l + 1;
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	for (i = 0; i < limit; i++)
		LCD_Write_DATA_hl(ch, cl);

	sbi(PORTB, (1 << PB4));
	resetXY();
}

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	ch = ((g_fcolor_red & 248) | g_fcolor_green >> 5);
	cl = ((g_fcolor_green & 28) << 3 | g_fcolor_blue >> 3);

	cbi(PORTB, (1 << PB4));
	setXY(x, y + radius, x, y + radius);
	LCD_Write_DATA_hl(ch,cl);
	setXY(x, y - radius, x, y - radius);
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		setXY(x - y1, y - x1, x - y1, y - x1);
		LCD_Write_DATA_hl(ch,cl);
	}
	sbi(PORTB, (1 << PB4));
	resetXY();
}

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
	int r2 = radius * radius;

	cbi(PORTB, (1 << PB4));

	for(y1 = -radius; y1 <= radius; y1++)
		for(x1 = -radius; x1 <= radius; x1++)
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					((g_fcolor_green & 28) << 3 | g_fcolor_blue >> 3));
			}

	sbi(PORTB, (1 << PB4));

	resetXY();
}
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
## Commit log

2017-05-21 initial project state
2017-05-21 ported LCD lib to C
2017-05-21 added drawing functionalities
2017-05-21 added link to wiki
2017-05-21 initial qtouch lib
2017-05-21 updated .gitignore
2017-05-21 cleaning
2017-05-22 renamed AVR header
2017-05-22 QTouch initial attempt
2017-05-22 qtouch second attempt
2017-05-23 removed QTouch due to data acquisition problems
2017-05-23 added support for MPU-6050 accelerometer
2017-05-23 updated project state: coding game logic
2017-05-25 game logic: stage 2
2017-05-25 updated level 1 design
2017-05-26 version 1.0
2017-08-24 reorder
2017-09-20 fix ball-paddle collision
2020-10-22 Create LICENSE + update README.

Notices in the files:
parts and their libraries:
SparkFun-Connectors: Licensing: CC v3.0 Share-Alike You are welcome to use this library for commercial purposes.
